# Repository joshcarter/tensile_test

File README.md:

# 3D Printed Plastic Tensile Strength

## Overview

I use this for measuring the tensile strength of 3D printed plastics.
There is a test fixture, an interface board, and program that runs on
a nearby laptop.

## Test Fixture

- Hi-Lift Jack
- Two clamps (see `printed_parts/Clamp.3mf`)
- 500kg S-type load cell
- HX711 load cell amplifier
- Rasperry Pi Pico interface board
- Laptop with USB connection to interface board

## Test Fixture Assembly

TODO: photo and instructions.

## Test Samples

See `printed_parts/Tensile test samples.3mf`. Note that the Z axis has
additional cross-sectional area since the Z axis is usually
substantially weaker.

## Interface Board

- Sparkfun HX711 load cell amplifier
- Raspberry Pi Pico

TODO: circuit schematic

The MicroPython code for the Pico is in the `pico` subdirectory.

## Python Requirements

    pip install -r requirements.txt

## Test Fixture Calibration

Initially the fixture will not be calibrated. Load code on the Pi Pico
(`pico/*.py) and it will output raw readings from the HX711.

Find some number of known calibration weights. I used kettlebells and
used a hanging scale to measure them as accurately as possible. These
readings (in KG) go into the `CAL_WEIGHTS` list in `utils.py`.

Run the calibration:

    python tensile_test.py calibrate --port /dev/cu.usbserial101

The first "known weight" should be no weight except the printed clamp.
Then add each known weight, pressing enter when the fixture is steady.

Finally, a `calibration.json` file will be written to this directory.
That file should be copied to the Pico. Once the Pico has its
calibration file it will output Newtons of force instead of raw HX711
readings.

## Running Tensile Tests

The main program is run like so:

    python tensile_test.py test \
      --port /dev/cu.usbserial101 \
      --type "PETG-CF" \
      --manufacturer "Atomic Filament" \
      --color "black" \
      --axis xy \

All test data will be output to a directory in the `data`
subdirectory, plus summary stats will be collected in `data/data.csv`.

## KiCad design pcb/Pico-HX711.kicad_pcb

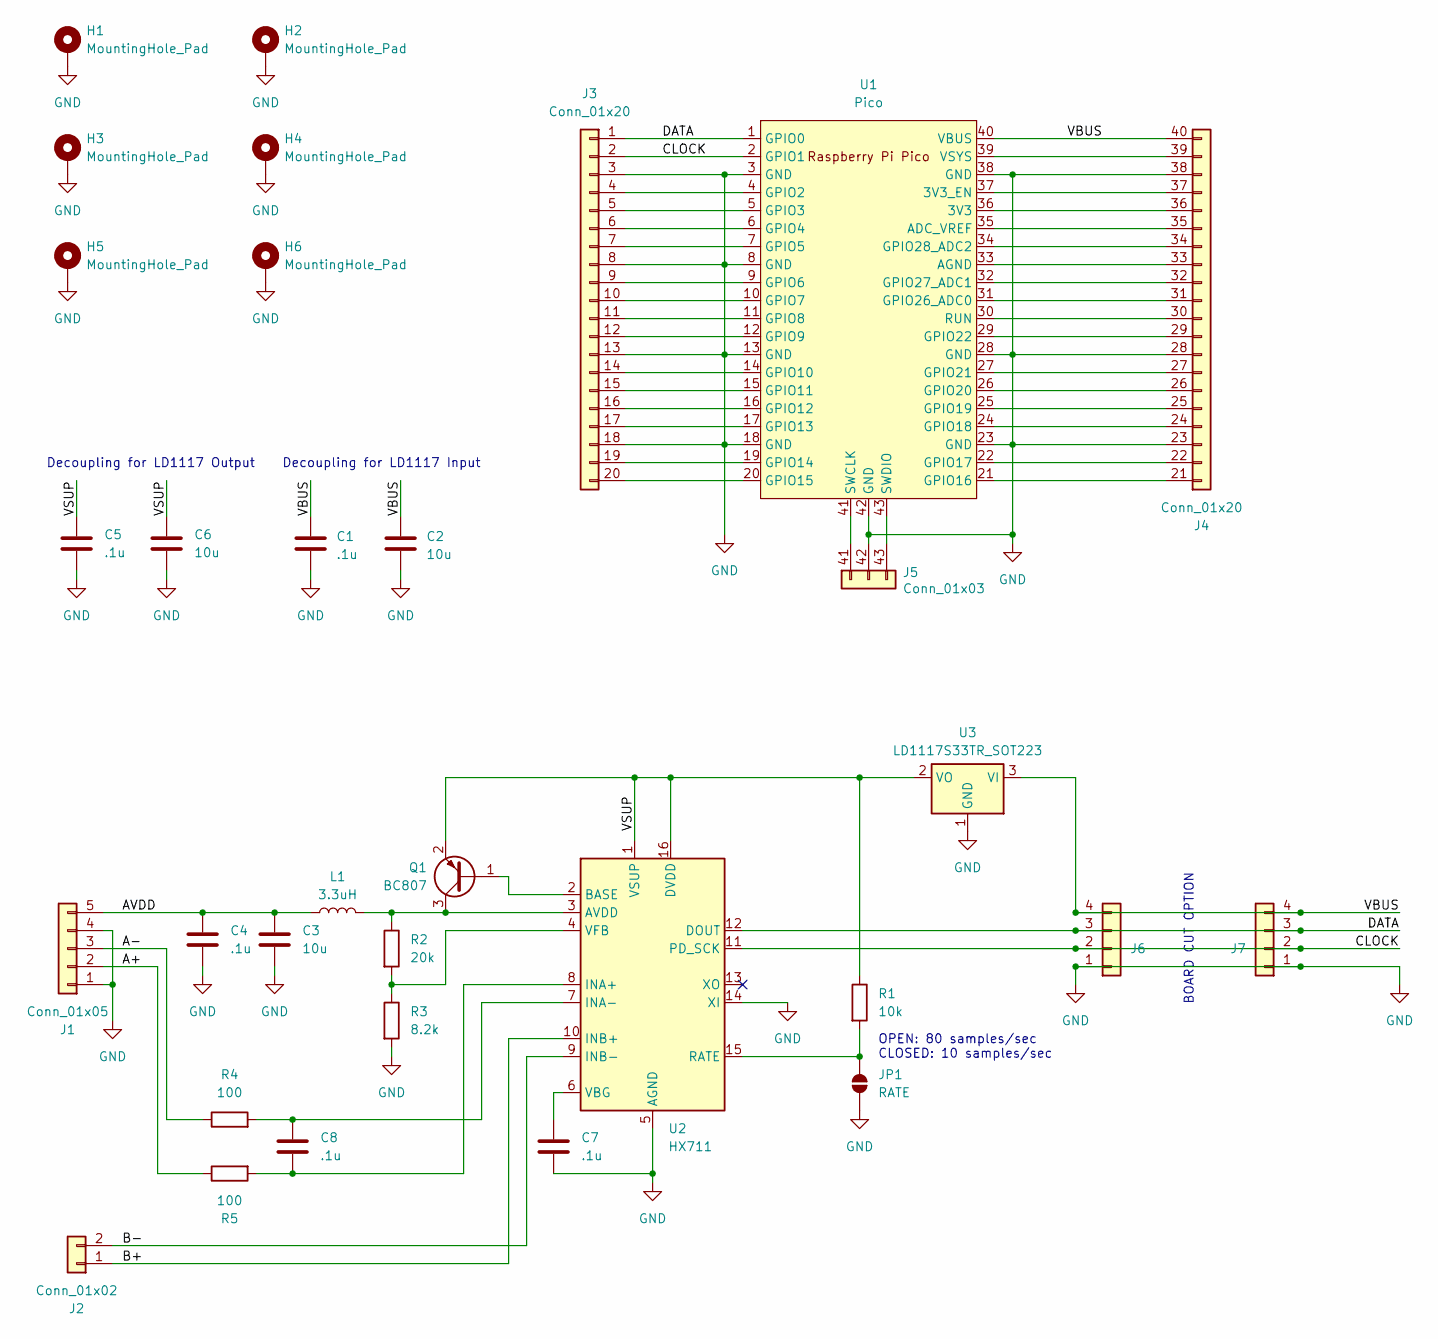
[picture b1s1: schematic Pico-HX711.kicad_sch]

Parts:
C1, C4, C5, C7, C8: .1u; C_0603_1608Metric
C2, C3, C6: 10u; C_1210_3225Metric
H1, H2, H3, H4, H5, H6: MountingHole_Pad; MountingHole_2.7mm_M2.5_Pad
J1: Conn_01x05; PinHeader_1x05_P2.54mm_Vertical
J2: Conn_01x02; PinHeader_1x02_P2.54mm_Vertical
J3: Conn_01x20; Pico_header_1
J4: Conn_01x20; Pico_header_2
J5: Conn_01x03; Pico_header_3
J6, J7: Conn_01x04; PinHeader_1x04_P2.54mm_Vertical
JP1: RATE; SolderJumper-2_P1.3mm_Open_RoundedPad1.0x1.5mm
L1: 3.3uH; L_0805_2012Metric
Q1: BC807; SOT-23
R1: 10k; R_0603_1608Metric
R2: 20k; R_0603_1608Metric
R3: 8.2k; R_0603_1608Metric
R4, R5: 100; R_0603_1608Metric
U1: Pico; RPi_Pico_SMD_TH
U2: HX711; SOIC-16_3.9x9.9mm_P1.27mm
U3: LD1117S33TR_SOT223; SOT-223-3_TabPin2

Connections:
/A+: J1.2, R5.1
/A-: J1.3, R4.1
/AVDD: C3.1, C4.1, J1.5, L1.1
/B+: J2.1, U2.10 (INB+)
/B-: J2.2, U2.9 (INB-)
/CLOCK: J3.2, J6.2, J7.2, U1.2 (GPIO1), U2.11 (PD_SCK)
/DATA: J3.1, J6.3, J7.3, U1.1 (GPIO0), U2.12 (DOUT)
/VBUS: C1.2, C2.2, J4.40 (Pin_20), J6.4, J7.4, U1.40 (VBUS), U3.3 (VI)
/VSUP: C5.1, C6.1, Q1.2 (E), R1.1, U2.1 (VSUP), U2.16 (DVDD), U3.2 (VO)
GND: C1.1, C2.1, C3.2, C4.2, C5.2, C6.2, C7.2, H1.1, H2.1, H3.1, H4.1, H5.1, H6.1, J1.1, J1.4, J3.3, J3.8, J3.13, J3.18, J4.23 (Pin_3), J4.28 (Pin_8), J4.38 (Pin_18), J5.42 (Pin_2), J6.1, J7.1, JP1.1 (A), R3.2, U1.3 (GND), U1.8 (GND), U1.13 (GND), U1.18 (GND), U1.23 (GND), U1.28 (GND), U1.38 (GND), U1.42 (GND), U2.5 (AGND), U2.14 (XI), U3.1 (GND)
unnamed: J3.4, U1.4 (GPIO2)
unnamed: J3.5, U1.5 (GPIO3)
unnamed: J3.6, U1.6 (GPIO4)
unnamed: J3.7, U1.7 (GPIO5)
unnamed: J3.9, U1.9 (GPIO6)
unnamed: J3.10, U1.10 (GPIO7)
unnamed: J3.11, U1.11 (GPIO8)
unnamed: J3.12, U1.12 (GPIO9)
unnamed: J3.14, U1.14 (GPIO10)
unnamed: J3.15, U1.15 (GPIO11)
unnamed: J3.16, U1.16 (GPIO12)
unnamed: J3.17, U1.17 (GPIO13)
unnamed: J3.19, U1.19 (GPIO14)
unnamed: J3.20, U1.20 (GPIO15)
unnamed: J4.21 (Pin_1), U1.21 (GPIO16)
unnamed: J4.22 (Pin_2), U1.22 (GPIO17)
unnamed: J4.24 (Pin_4), U1.24 (GPIO18)
unnamed: J4.25 (Pin_5), U1.25 (GPIO19)
unnamed: J4.26 (Pin_6), U1.26 (GPIO20)
unnamed: J4.27 (Pin_7), U1.27 (GPIO21)
unnamed: J4.29 (Pin_9), U1.29 (GPIO22)
unnamed: J4.30 (Pin_10), U1.30 (RUN)
unnamed: J4.31 (Pin_11), U1.31 (GPIO26_ADC0)
unnamed: J4.32 (Pin_12), U1.32 (GPIO27_ADC1)
unnamed: J4.33 (Pin_13), U1.33 (AGND)
unnamed: J4.34 (Pin_14), U1.34 (GPIO28_ADC2)
unnamed: J4.35 (Pin_15), U1.35 (ADC_VREF)
unnamed: J4.36 (Pin_16), U1.36 (3V3)
unnamed: J4.37 (Pin_17), U1.37 (3V3_EN)
unnamed: J4.39 (Pin_19), U1.39 (VSYS)
unnamed: J5.41 (Pin_1), U1.41 (SWCLK)
unnamed: J5.43 (Pin_3), U1.43 (SWDIO)
unnamed: JP1.2 (B), R1.2, U2.15 (RATE)
unnamed: Q1.1 (B), U2.2 (BASE)
unnamed: L1.2, Q1.3 (C), R2.1, U2.3 (AVDD)
unnamed: C8.2, R5.2, U2.8 (INA+)
unnamed: C8.1, R4.2, U2.7 (INA-)
unnamed: C7.1, U2.6 (VBG)
unnamed: R2.2, R3.1, U2.4 (VFB)

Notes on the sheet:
BOARD CUT OPTION
OPEN: 80 samples/sec CLOSED: 10 samples/sec
Decoupling for LD1117 Output
Decoupling for LD1117 Input

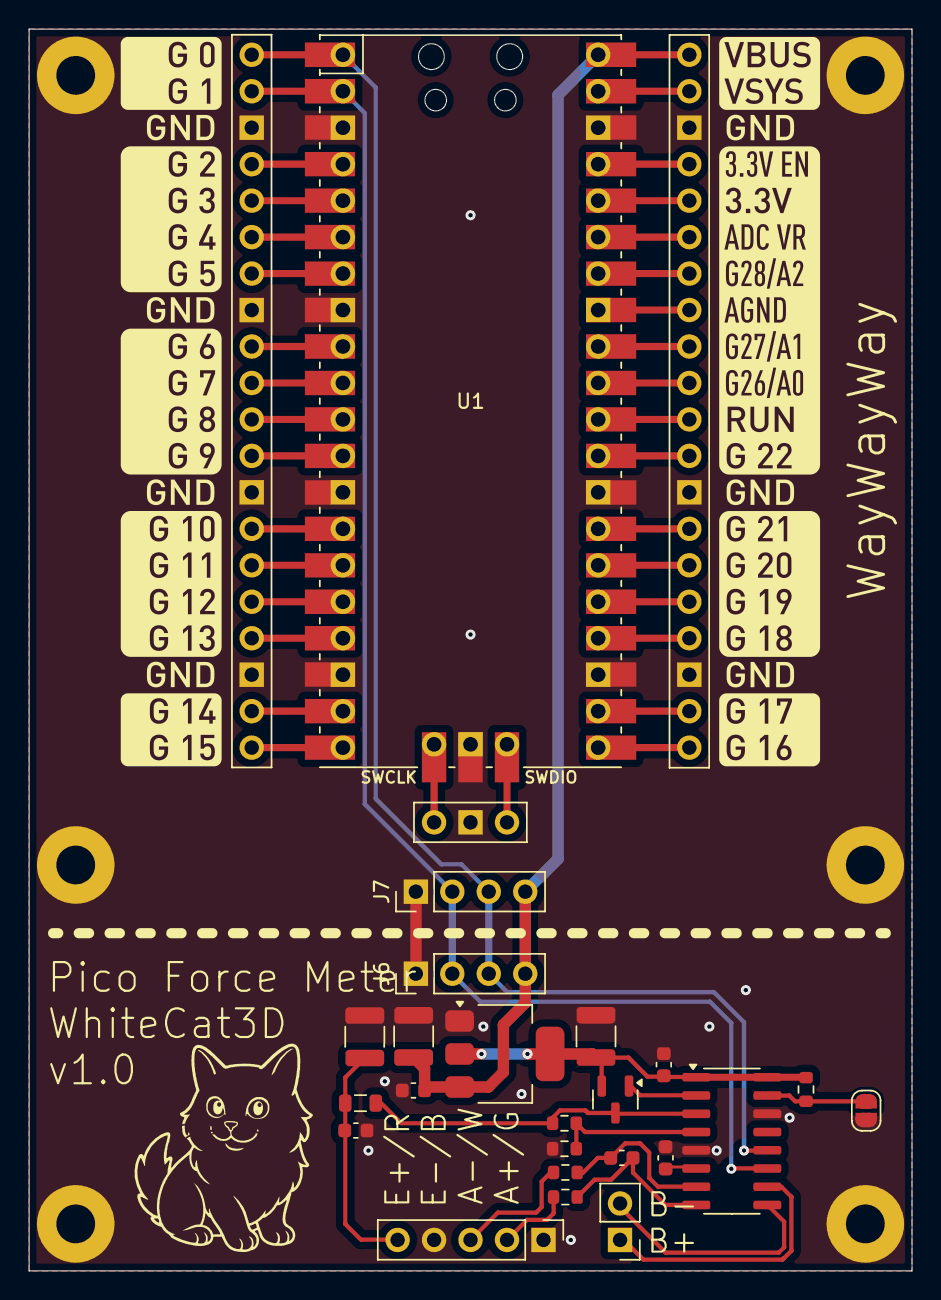
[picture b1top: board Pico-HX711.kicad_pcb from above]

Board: 2 copper layers, 61.5 x 86.5 mm, 32 parts (0 on the bottom side), 49 nets.

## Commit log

2025-08-03 Adding printed parts and current data.
2025-08-03 initial import
2025-08-03 Working.
2025-08-03 working on calibration
2025-08-03 TK GUI (not quite working).
2025-08-03 removing old arduino code; renaming Pico MicroPython code.
2025-08-03 updating readme.
2025-08-03 Better logging and summary result printing.
2025-08-03 fixed calibration (?)
2025-08-03 switching calibration to linear regression.
2025-08-03 new calibration.json with 80hz hx711.
2025-08-03 Polymaker PET-CF
2025-08-03 adding more test data.
2025-08-03 adding requirements.txt
2025-08-04 adding config file.
2025-08-04 adding config reader, new data columns.
2025-08-04 adding more serial options
2025-08-04 bug fix for serial reader
2025-08-05 more data
2025-08-06 updated printed parts; larger clamp variant
2025-08-07 working on new pico code.
2025-08-08 fixing pico code.
2025-08-08 improving pico code
2025-08-08 fixing serial stalls on pico
2025-08-08 fixing issue in calibrate on bad serial read.
2025-08-08 integrating with changes in pico serial data.
2025-08-08 wip refactoring with claude code.
2025-08-08 refactoring into more python files.
2025-08-08 adding current version of python code.
2025-08-09 adding more test results
2025-08-09 removing some old data
2025-08-09 fixes in test app.
2025-08-12 working on cleaner handling of serial resets.
2025-08-17 code refactoring and updated 50/25mm2 printed parts.
2025-08-18 New test data; fixing regression in test_app.
2025-08-18 New test sample and clamp design
2025-08-18 Siraya Tech ASA-GF
2025-08-19 test samples with fewer sprues.
2025-08-19 moving STLs into their own directory.
2025-08-19 new readme.
2025-08-19 updating printed parts
2025-08-19 adding STEP for clamp.
2025-08-24 minor mods
2025-08-25 more test data on PLA variants
2025-08-25 removing old data format.
2025-08-30 test data for ABS, ASA with CF and GF
2025-09-01 adding newest round of PET test data.
2025-09-01 ordering test data by XY tensile strength
2025-09-08 data for PETG in 4 colors; new tester with Z axis brim.
2025-09-11 add output of lb-ft and psi
2025-09-11 more test data
2025-09-17 Adding PCB.
2026-05-30 test data
2026-06-07 New test sample parts.
2026-06-07 New pico code to fix intermittent HX711 invalid read errors.
2026-06-07 .gitignore, CLAUDE.md
